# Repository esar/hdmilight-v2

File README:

For latest version, go to http://hacks.esar.org.uk/

How to use:

1) Manufacture the HDMI receiver board that can be found in 
   the 'board' directory (CADSoft Eagle format).
2) Open the 'fpga/hdmilight.xise' project in Xilinx ISE and
   generate a bit file.
3) Edit the files under the config directory to configure
   the LEDs.
4) Edit 'Makefile' in the top level directory and set
   the DATA2MEM path for the Xilinx data2mem tool location
   on your system.
5) Run 'make' in the top level directory, which will build
   'tools/makemem', then the firmware image, then the config
   files, before merging the firmware and config into the
   final bitfile.
   The final result should be hdmilight.bit in the top
   level directory.
6) Upload hdmilight.bit to a Papilio Pro FPGA board
7) Install the HDMI receiver board on to the Papilio board.
8) Connect LED strips to output pins
9) Open a serial terminal to the Papilio
10) Connect HDMI source to receiver board
11) It should now be working.

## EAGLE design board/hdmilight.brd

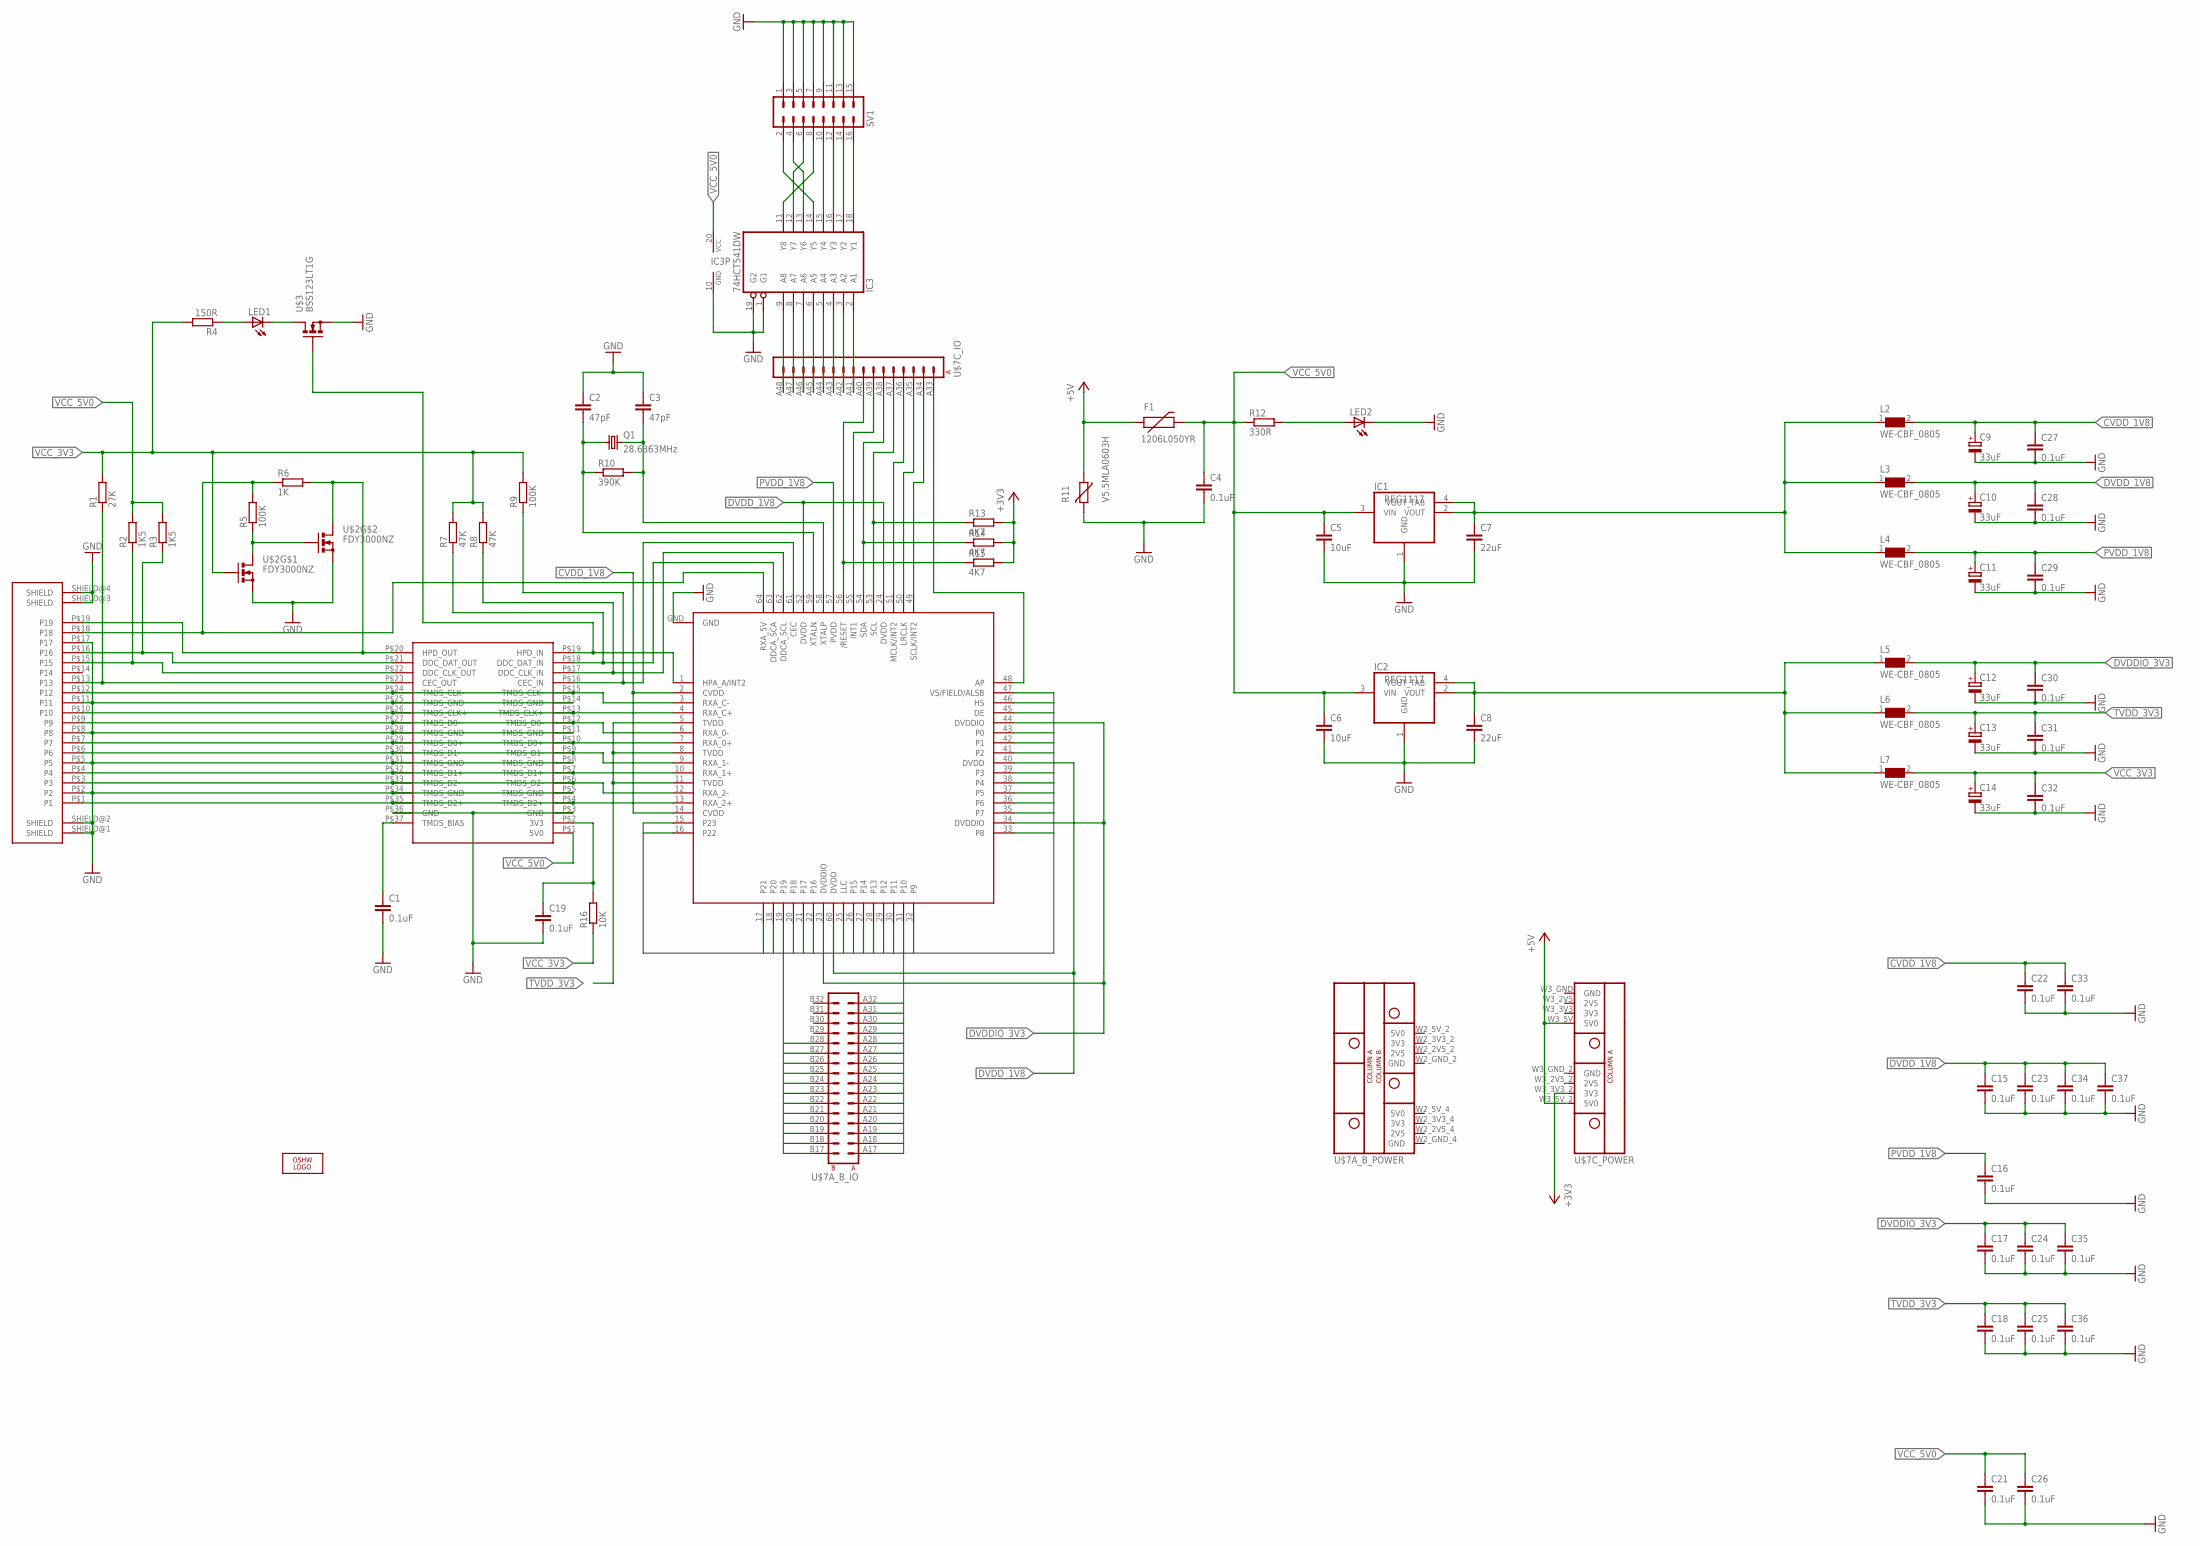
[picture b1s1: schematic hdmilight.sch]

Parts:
C1, C4, C16, C17, C19, C21, C22, C24, C26, C27, C28, C29, C30, C31, C32, C33: 0.1uF; C0603
C2, C3: 47pF; C0603
C5, C6: 10uF; C1210
C7, C8: 22uF; C1206
C9, C10, C11, C12, C13, C14: 33uF; SMC_B
C15, C18, C23, C25, C34, C35, C36, C37: 0.1uF; C0402
F1: 1206L050YR; PTC-1206
IC1, IC2: REG1117; SOT223
IC3: 74HCT541DW; SO20W
L2, L3, L4, L5, L6, L7: WE-CBF_0805; 0805
LED1, LED2: LEDCHIP-LED0805; CHIP-LED0805
LOGO1: OSHW_LOGO_FILLX0200-NT; OSHW_FILLX200_NOTEXT
Q1: 28.6363MHz; SM49
R1: 27K; R0603
R2, R3: 1K5; R0603
R4: 150R; R0603
R5, R9: 100K; R0603
R6: 1K; R0603
R7, R8: 47K; R0603
R10: 390K; R0603
R11: V5.5MLA0603H; CT/CN0603
R12: 330R; R0603
R13, R14, R15: 4K7; R0603
R16: 10K; R0603
SV1: MA08-2
U$1: FCI_HDMI_SOCKET_10029449-001RCF
U$2: FDY3000NZ; SC89-6
U$3: BSS123LT1G; SOT23
U$4: TPD12S520; TSSOP38
U$6: ADV7611; TQFP64-10X10
U$7: MEGAWING_FULL_P1MEGAWING_P1; MEGAWING_FULL_NOHOLES_P1

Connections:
+3V3: R13.2, R14.2, R15.2, U$7.W3_3V3_2 (3V3)
+5V: F1.1, R11.1, U$7.W3_5V (5V0), U$7.W3_5V_2 (5V0)
CVDD_1V8: C9.+, C22.1, C27.1, C33.1, L2.2, U$6.2 (CVDD), U$6.14 (CVDD)
DE: U$6.45 (DE), U$7.B18 (B2)
DVDDIO_3V3: C12.+, C17.1, C24.1, C30.1, C35.1, L5.2, U$6.23 (DVDDIO), U$6.34 (DVDDIO), U$6.44 (DVDDIO)
DVDD_1V8: C10.+, C15.1, C23.1, C28.1, C34.1, C37.1, L3.2, U$6.24 (DVDD), U$6.40 (DVDD), U$6.52 (DVDD), U$6.60 (DVDD)
GND: C1.2, C2.1, C3.1, C4.2, C5.2, C6.2, C7.2, C8.2, C9.-, C10.-, C11.-, C12.-, C13.-, C14.-, C15.2, C16.2, C17.2, C18.2, C19.2, C21.2, C22.2, C23.2, C24.2, C25.2, C26.2, C27.2, C28.2, C29.2, C30.2, C31.2, C32.2, C33.2, C34.2, C35.2, C36.2, C37.2, IC1.1 (GND), IC2.1 (GND), IC3.1 (G1), IC3.10 (GND), IC3.19 (G2), LED2.C, R11.2, SV1.1, SV1.3, SV1.5, SV1.7, SV1.9, SV1.11, SV1.13, SV1.15, U$1.P$2 (P2), U$1.P$5 (P5), U$1.P$8 (P8), U$1.P$11 (P11), U$1.P$17 (P17), U$1.SHIELD@1 (SHIELD), U$1.SHIELD@2 (SHIELD), U$1.SHIELD@3 (SHIELD), U$1.SHIELD@4 (SHIELD), U$2.P$1 (S), U$2.P$4 (S), U$3.2 (S), U$4.P$3 (GND), U$4.P$5 (TMDS_GND), U$4.P$8 (TMDS_GND), U$4.P$11 (TMDS_GND), U$4.P$14 (TMDS_GND), U$4.P$25 (TMDS_GND), U$4.P$28 (TMDS_GND), U$4.P$31 (TMDS_GND), U$4.P$34 (TMDS_GND), U$4.P$36 (GND), U$6.GND, U$7.W2_GND_2 (GND), U$7.W2_GND_4 (GND), U$7.W3_GND (GND), U$7.W3_GND_2 (GND)
HS: U$6.46 (HS), U$7.A17 (A1)
LLC: U$6.25 (LLC), U$7.A30 (A14)
unnamed: U$1.P$1 (P1), U$4.P$4 (TMDS_D2+), U$4.P$35 (TMDS_D2+), U$6.13 (RXA_2+)
unnamed: U$1.P$3 (P3), U$4.P$6 (TMDS_D2-), U$4.P$33 (TMDS_D2-), U$6.12 (RXA_2-)
unnamed: U$1.P$4 (P4), U$4.P$7 (TMDS_D1+), U$4.P$32 (TMDS_D1+), U$6.10 (RXA_1+)
unnamed: U$1.P$6 (P6), U$4.P$9 (TMDS_D1-), U$4.P$30 (TMDS_D1-), U$6.9 (RXA_1-)
unnamed: U$1.P$7 (P7), U$4.P$10 (TMDS_D0+), U$4.P$29 (TMDS_D0+), U$6.7 (RXA_0+)
unnamed: U$1.P$9 (P9), U$4.P$12 (TMDS_D0-), U$4.P$27 (TMDS_D0-), U$6.6 (RXA_0-)
unnamed: U$1.P$10 (P10), U$4.P$13 (TMDS_CLK+), U$4.P$26 (TMDS_CLK+), U$6.4 (RXA_C+)
unnamed: U$1.P$12 (P12), U$4.P$15 (TMDS_CLK-), U$4.P$24 (TMDS_CLK-), U$6.3 (RXA_C-)
unnamed: IC3.9 (A8), U$7.A48 (A16)
unnamed: IC3.8 (A7), U$7.A47 (A15)
unnamed: IC3.7 (A6), U$7.A46 (A14)
unnamed: IC3.6 (A5), U$7.A45 (A13)
unnamed: R1.1, U$1.P$13 (P13), U$4.P$23 (CEC_OUT)
unnamed: R2.1, U$1.P$15 (P15), U$4.P$22 (DDC_CLK_OUT)
unnamed: R3.1, U$1.P$16 (P16), U$4.P$21 (DDC_DAT_OUT)
unnamed: R6.2, U$1.P$19 (P19), U$2.P$3 (D), U$4.P$20 (HPD_OUT)
unnamed: IC3.5 (A4), U$7.A44 (A12)
unnamed: IC3.4 (A3), U$7.A43 (A11)
unnamed: LED2.A, R12.2
unnamed: R8.1, U$4.P$17 (DDC_CLK_IN), U$6.62 (DDCA_SCL)
unnamed: C8.1, IC2.2 (VOUT), IC2.4 (VOUT_TAB), L5.1, L6.1, L7.1
unnamed: C7.1, IC1.2 (VOUT), IC1.4 (VOUT_TAB), L2.1, L3.1, L4.1
unnamed: R7.1, U$4.P$18 (DDC_DAT_IN), U$6.63 (DDCA_SCA)
unnamed: R9.1, U$4.P$16 (CEC_IN), U$6.61 (CEC)
unnamed: C2.2, Q1.1, R10.1, U$6.59 (XTALN)
unnamed: C3.2, Q1.2, R10.2, U$6.58 (XTALP)
unnamed: U$6.49 (SCLK/INT2), U$7.A34 (A2)
unnamed: U$6.50 (LRCLK), U$7.A35 (A3)
unnamed: U$6.48 (AP), U$7.A33 (A1)
unnamed: R13.1, U$6.53 (SCL), U$7.A37 (A5)
unnamed: R14.1, U$6.54 (SDA), U$7.A38 (A6)
unnamed: U$6.55 (INT1), U$7.A39 (A7)
unnamed: R15.1, U$6.56 (/RESET), U$7.A40 (A8)
unnamed: C1.1, U$4.P$37 (TMDS_BIAS)
unnamed: IC3.3 (A2), U$7.A42 (A10)
unnamed: IC3.2 (A1), U$7.A41 (A9)
unnamed: IC3.14 (Y5), SV1.2
unnamed: IC3.11 (Y8), SV1.8
unnamed: IC3.12 (Y7), SV1.6
unnamed: IC3.13 (Y6), SV1.4
unnamed: IC3.15 (Y4), SV1.10
unnamed: IC3.16 (Y3), SV1.12
unnamed: U$6.51 (MCLK/INT2), U$7.A36 (A4)
unnamed: IC3.17 (Y2), SV1.14
unnamed: IC3.18 (Y1), SV1.16
unnamed: C19.1, R16.2, U$4.P$2 (3V3)
unnamed: R5.1, U$2.P$5 (G), U$2.P$6 (D)
unnamed: R5.2, R6.1, U$1.P$18 (P18), U$6.64 (RXA_5V)
unnamed: LED1.A, R4.1
unnamed: LED1.C, U$3.3 (D)
unnamed: U$3.1 (G), U$4.P$19 (HPD_IN), U$6.1 (HPA_A/INT2)
P0: U$6.43 (P0), U$7.A18 (A2)
P1: U$6.42 (P1), U$7.B19 (B3)
P2: U$6.41 (P2), U$7.A19 (A3)
P3: U$6.39 (P3), U$7.B20 (B4)
P4: U$6.38 (P4), U$7.A20 (A4)
P5: U$6.37 (P5), U$7.B21 (B5)
P6: U$6.36 (P6), U$7.A21 (A5)
P7: U$6.35 (P7), U$7.B22 (B6)
P8: U$6.33 (P8), U$7.A22 (A6)
P9: U$6.32 (P9), U$7.B23 (B7)
P10: U$6.31 (P10), U$7.A23 (A7)
P11: U$6.30 (P11), U$7.B24 (B8)
P12: U$6.29 (P12), U$7.A24 (A8)
P13: U$6.28 (P13), U$7.B25 (B9)
P14: U$6.27 (P14), U$7.A25 (A9)
P15: U$6.26 (P15), U$7.B26 (B10)
P16: U$6.22 (P16), U$7.A26 (A10)
P17: U$6.21 (P17), U$7.B27 (B11)
P18: U$6.20 (P18), U$7.A27 (A11)
P19: U$6.19, U$7.B28 (B12)
P20: U$6.18 (P20), U$7.A28 (A12)
P21: U$6.17 (P21), U$7.A29 (A13)
P22: U$6.16 (P22), U$7.A31 (A15)
P23: U$6.15 (P23), U$7.A32 (A16)
PVDD_1V8: C11.+, C16.1, C29.1, L4.2, U$6.57 (PVDD)
TVDD_3V3: C13.+, C18.1, C25.1, C31.1, C36.1, L6.2, U$6.5 (TVDD), U$6.8 (TVDD), U$6.11 (TVDD)
VCC_3V3: C14.+, C32.1, L7.2, R1.2, R4.2, R7.2, R8.2, R9.2, R16.1, U$2.P$2 (G)
VCC_5V0: C4.1, C5.1, C6.1, C21.1, C26.1, F1.2, IC1.3 (VIN), IC2.3 (VIN), IC3.20 (VCC), R2.2, R3.2, R12.1, U$4.P$1 (5V0)
VS: U$6.47 (VS/FIELD/ALSB), U$7.B17 (B1)

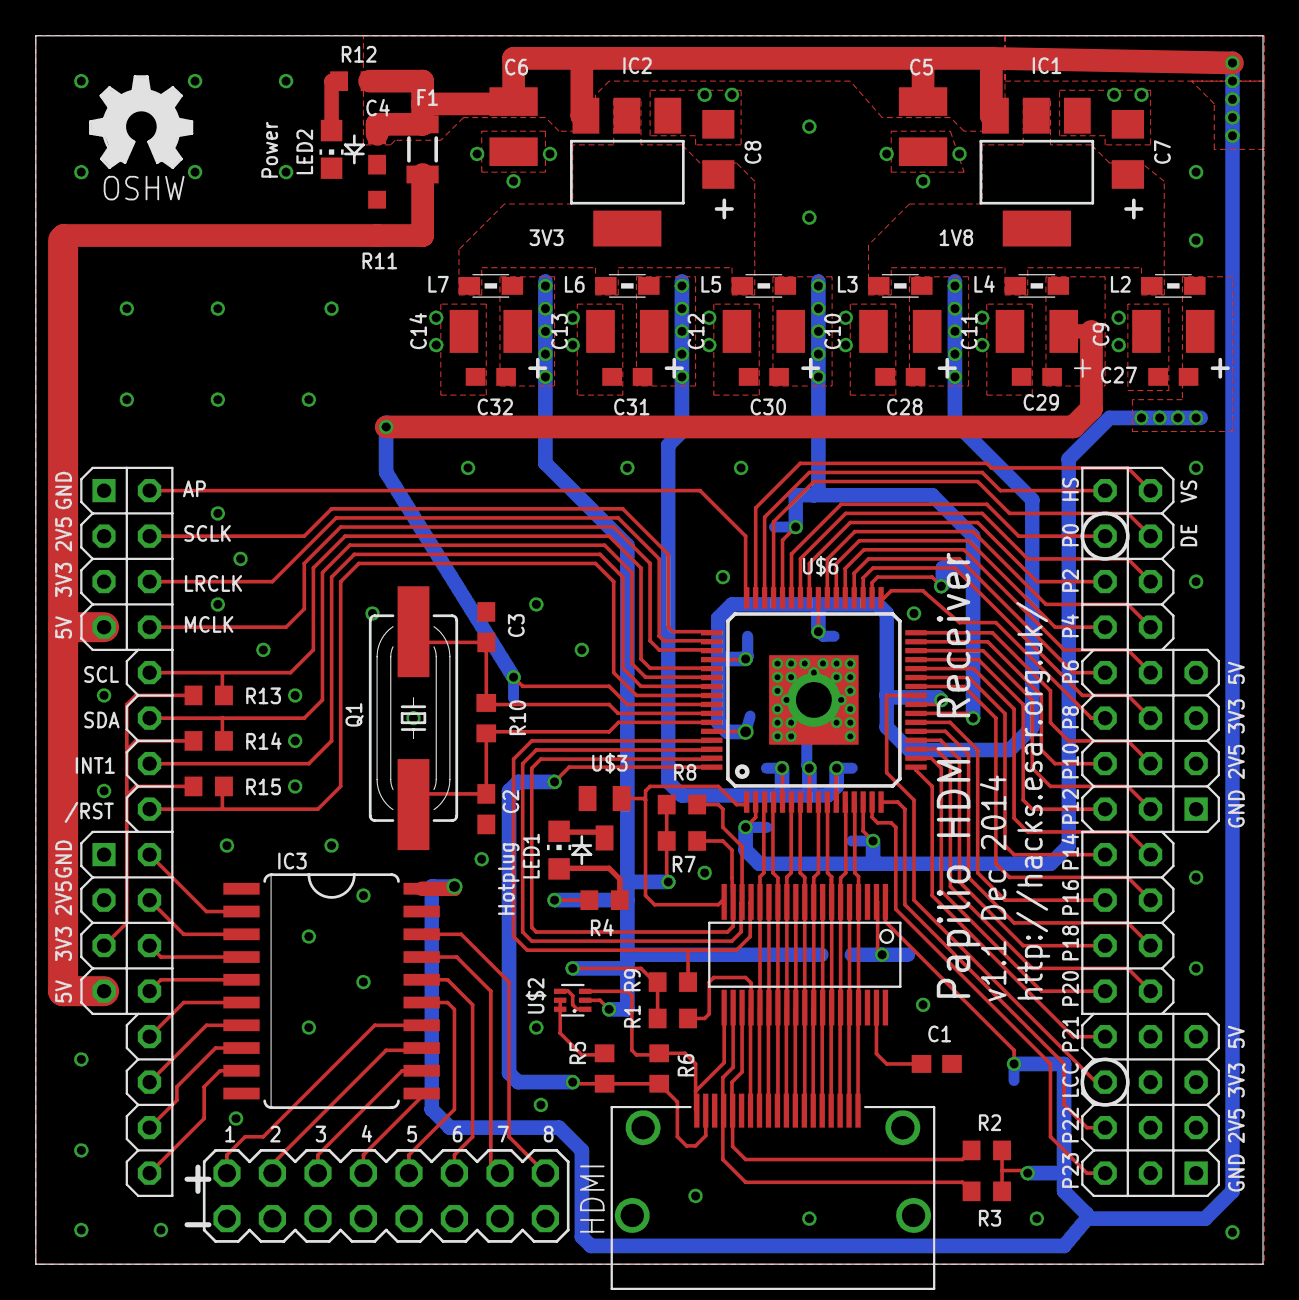
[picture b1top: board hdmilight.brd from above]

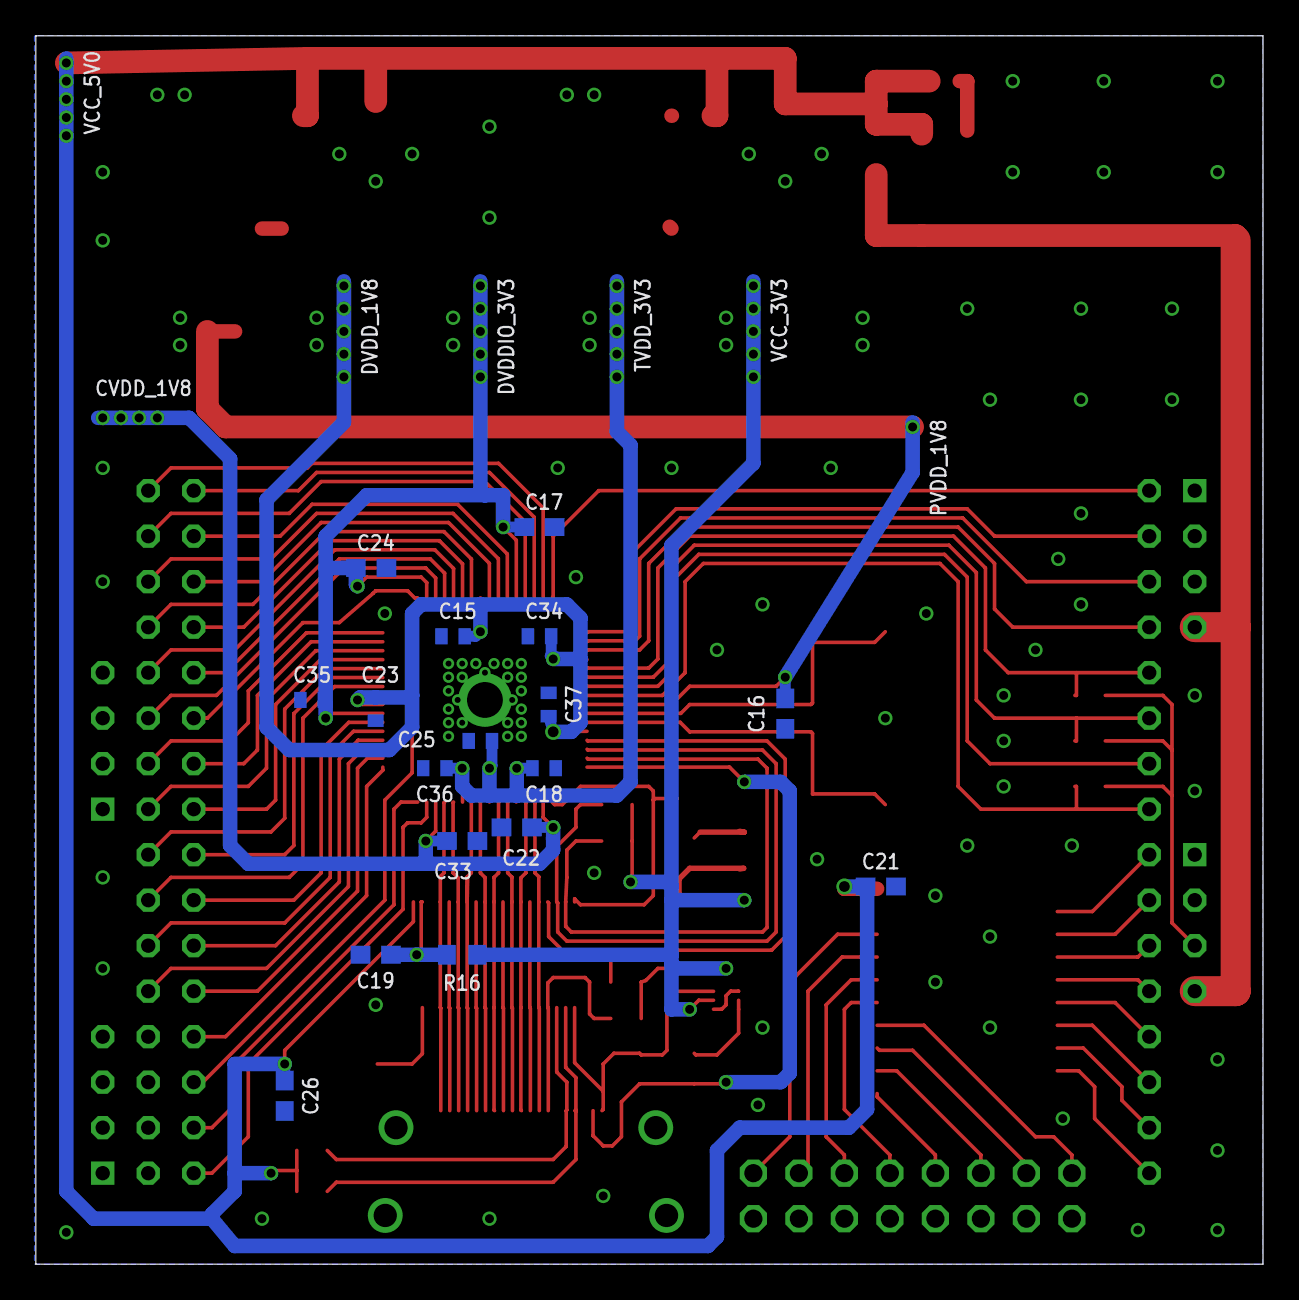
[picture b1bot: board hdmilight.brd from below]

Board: 2 copper layers, 68.5 x 68.6 mm, 73 parts (17 on the bottom side), 89 nets.

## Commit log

2013-11-26 Initial import
2013-11-26 Added missing vhd files for block RAMs
2013-12-01 Added hgignore file
2013-12-01 Added missing makemem step to firmware generation, automated merge into bitfile, updated build instructions
2013-12-02 changed firmware to automatically apply configuration at powerup
2013-12-02 updated default light definitions
2013-12-02 Added PNG of HDMI board schematic
2014-08-30 Fixed firmware build errors with avr-gcc 4.8
2014-10-18 Ported to Papilio Pro Spartan6 LX9
2014-10-18 Replaced coregen block rams with generic vhdl
2014-10-18 Added support for delaying output by up to 8 frames. Currently untested and missing configuration interface
2014-10-19 Reworked configuration interface to allow for multiple config rams and registers
2014-10-22 Extended AVR program ROM from 8KB to 16KB
2014-10-26 Added per output colour transformation, per output gamma correction, output mapping table for each output to select area/colour-coefficients/gamma-table for up to 512 LEDs per output (4096 total LEDs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
2014-11-02 changed to register video data immediately
2014-11-02 added timing constraints for video data inputs
2014-11-02 fixed result retreival debug interface
2014-11-02 fixed vblank output of resultDelay so that it's a single clock pulse
2014-11-02 added synchronisation of hsync and vsync signals for each clock domain
2014-11-02 reduced drive strength of outputs in an attempt to reduce noise induced into vsync
2014-11-02 fixed mappings for outputConfigRam's 16 bit port
2014-11-02 updated firmware to fix setting of colour coefficients
2014-11-03 split firmware command handlers into separate source files
2014-11-04 added temporal smoothing
2014-11-05 mapped configuration RAM and registers directly into AVR address space rather than communicating through I/O ports
2014-11-05 fixed comments in resultDelay to reflect changes for temporal smoothing
2014-11-05 updated firmware to allow entry of colour coefficients and temporal smoothing ratio with a decimal point
2014-11-06 updated GetColour and GetDelay firmware commands to show results as a number with a decimal point rather than as raw bytes
2014-11-08 fixed I2C firmware Get/Set commands to allow access to all devices not just the mapper
2014-11-08 moved EDID from the main ADV7611 I2C config table to its own file for easier maintenance, also updated EDID content to declare 1920x1080 as native resolution
2014-11-08 tweaked LLC clock delay for more reliable aquisition of pixel bus data
2014-11-09 added clock enable to AVR CPU to allow it to be stopped during DMA transfers
2014-11-09 added flashDMAController to perform transfers between flash and AVR/ambilight address space, reading mostly working, writing not supported yet
2014-11-10 added storage of multiple configurations in flash at build time
2014-11-14 fixed value of HDMI pull up resistors on receiver board
2014-11-14 added ODDR2 to forward clock to SPI clock pin so the clock doesn't need to leave the clock nets and enter the main fabric
2014-11-16 added letterbox/pillarbox detection
2014-11-16 added missing file test_configRam.vhd
2014-11-23 fixed halting CPU during DMA transfers
2014-11-23 changed formatDetector to use DE instead of HSYNC to eliminate front and back porch
2014-11-23 rewritten firmware side of letter/pillarbox detection, now loading different configs from flash when format changes
2014-11-23 fixed config address generation, added third set of config files for 1.33:1
2014-11-24 general firmware cleanup: config commands renamed to reset, light commands renamed to areas, better help text, area config table removed, old printf files removed
2014-11-24 fixed 'clean' targets in makefiles
2014-12-01 moved .hgignore to .gitignore
2014-12-01 tools/output2bin.py: fixed swapped gamma/colour
2014-12-01 added missing file: firmware/cmd_mem.c
2014-12-02 added enable/disable format change firmware commands
2014-12-03 updated makefile to override stack location to take advantage of the full 2KB of available RAM
2014-12-03 fixed skipping of disabled LEDs when distributing results to outputs
2014-12-05 changed scaler to use DE (data enable) instead of HSYNC to eliminate front and back porches
2014-12-05 removed (now redundant) 'output' from area config
2014-12-05 changed output map to have 8-bit area instead of 9-bit and 4-bit colour instead of 3-bit
2014-12-05 simplified outputConfigRam implementation
2014-12-13 updated output2bin.py for changes to width of area and colour
2014-12-13 added brightness/contrast/saturation control to colour config files
2014-12-13 docs: added block diagram
2014-12-13 moved RGB->GRB channel swapping to resultDistributor so that colour matrix and gamma channel order is as advertised
2014-12-13 docs: started documenting serial commands
2014-12-14 updated README for v2 changes
2014-12-21 added missing capacitor values to schematic
2014-12-21 removed power jack from HDMI receiver board
2014-12-22 receiver board: replaced TXB0108 level shifter with a 74HCT541
2014-12-22 receiver board: changed value of IP4776CZ38 ESD protection IC to TPD12S520
2014-12-23 receiver board: merged changes from Jet:
    * added "power" and "hotplug" LED labels
    * added LED polarity symbols
    * moved C7/C8 labels off of vias
    * moved vias from under SCL and RST labels
    * moved vias from under R13/14/15 labels
    * added + symbols on polarised caps C7-14
2014-12-23 receiver board: added BOM created by Jet after the following minor changes:
    * removed C20
    * changed C35 from 0603 to 0402
    * removed power jack
    * changed 74HCT245 to 74HCT541
    * C1, C4, etc.: changed Farnell part number to a X7R part
2014-12-27 receiver board: fixed unrouted wire on C35 spotted by Jet
2014-12-27 receiver board: fixed wrong Mouser part number for 74HCT541, spotted by Jet
2014-12-31 receiver board: updated BOM: fixed total count for 0.1uF capacitors and removed non-existant R17, R19
2014-12-31 receiver board: BOM: added 2x4 stackable socket to pass through unused pins
2014-12-31 receiver board: added v1.1 gerbers
2015-01-31 Patch from Jet: Made PROGMEM variables const to fix compiling with newer versions of avr-gcc and re-enabled automatic initialisation
2015-01-31 receiver board: removed untested warning from v1.1 gerbers zip file
2015-01-31 receiver board: removed untested warning from Eagle CAD board layout
2015-01-31 receiver board: renamed BOM to BOM-v1.1
2015-01-31 receiver board: added PNG of v1.1 schematic
2015-02-01 updated .ucf file for v1.1 receiver board
2015-02-04 updated .ucf file for output pin ordering on v1.1 receiver board
2015-02-04 Added ConfigGenerate utility from Jet
2015-02-06 Fixed BST instruction bug in AVR core, it was inverting the bit
2015-02-06 Fixed Get I2C firmware command, it was always reading from device 0x98. Also added bit range option to command.
2015-02-06 Fixed HDMI input colour space selection, was forced to RGB, now auto selecting based on HDMI Info Frames Issue discovered by Jet
2015-02-06 Updated GetFormat command to display current active resolution and aspect ratio in addition to the existing raw values from the format detector
2015-02-07 Adding Makefile and license to ConfigGenerate.c
2015-02-07 Added Letterbox capability to speed up generating letterbox configurations from a given working configuration
2015-02-08 Format changed interrupt now stays raised until cleared via write to port, ADV7611 INT1 made available to firmware
2015-02-08 added i2cWrite() function to remove duplicated code
2015-02-08 Started support for control via CEC Remote Pass Through Currently supports: * turning on/off * global brightness/contrast/hue/saturation * loading one of first 8 configurations (and disabling auto sw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
    All key codes are currently hard-coded
    Currently needs to be manually enabled via RK console command
2015-02-08 changed off colour to black
2015-02-08 Changed LLC phase to 0x99 for new board v2
2015-02-14 fixed bugs in serial terminal command history when wrapping around the ring buffer
2015-02-15 Fixed CPU resets and other random behaviour when an interrupt is received during a DMA transfer
2015-02-15 Added firmware command to measure free memory (area between globals and stack)
2015-02-15 Made CEC remote control keys configurable via config/keys.conf
2015-02-15 Reduced drive strength of all signals from ADV7611 to combat unstable vsync
2015-04-02 Update BOM-v1.1
    Updated Farnell supplier codes
2015-04-08 Connected the four unused pins to lower 4 bits of PORTD in AVR, used first pin as power on/off signal.
2015-08-20 Disabled power switch by default as it requires extra hardware
2015-08-22 updated python scripts to work with python version 2 and 3
2015-08-25 Fixed output of binary data from python scripts on windows
2015-11-28 Increased AVR program memory from 16KB to 24KB

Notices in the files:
parts and their libraries:
EagleLibrary_Wuerth_Elektronik_eiSos_Ver: Copyright: Würth Elektronik
